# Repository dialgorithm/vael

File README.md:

<h1 align="center">
  vael
  <br>
</h1>

<h4 align="center">
esp32-s3 n8r8 flight controller for sensing and data logging.
</h4>

## it features

- **ESP32-S3-WROOM-1-N8R8** as the main controller
- **MPU6050** 3-axis accelerometer and gyroscope for motion and orientation data
- **BMP180** digital pressure sensor for pressure and altitude-related measurements
- **MicroSD card storage** for flight data logging
- **USB-C connectivity** for programming, debugging, and data transfer
- **TP4056-based LiPo charging** circuitry
- **DW01A battery protection** for LiPo protection
- **MT3608 boost converter** for generating the required higher-voltage rail
- **AMS1117-3.3 LDO** for regulated 3.3 V power
- **USBLC6-2SC6 ESD protection** for USB protection

## design

**vael** is designed to keep the electronics compact while providing enough space for sensors, power circuitry, storage, and connectivity.

the board is built around the **esp32-s3-wroom-1-n8r8**, with the supporting electronics integrated onto a custom pcb. it combines the **imu, pressure sensor, microsd storage, usb-c interface, battery charging, protection, and voltage regulation** into a single compact board.

the layout keeps the sensing and processing electronics centralized while separating the power and signal sections. the **mpu6050** and **bmp180** are positioned for consistent sensor measurements, while the **microsd slot, usb-c connector, battery connector, reset button, and mode switch** are accessible from the board edges.

the board primarily uses **smd components**, including 1206 passives and compact sensor packages, to maintain a small form factor while providing the hardware required for **data collection, logging, and embedded flight applications**.

## Schematics + PCB

| Schematic                           | PCB                    | 3d                       |
| ----------------------------------- | ---------------------- | ------------------------ |
|  |  |  |

## BOM

the complete bill of materials is available in [`bom.csv`](bom.csv).

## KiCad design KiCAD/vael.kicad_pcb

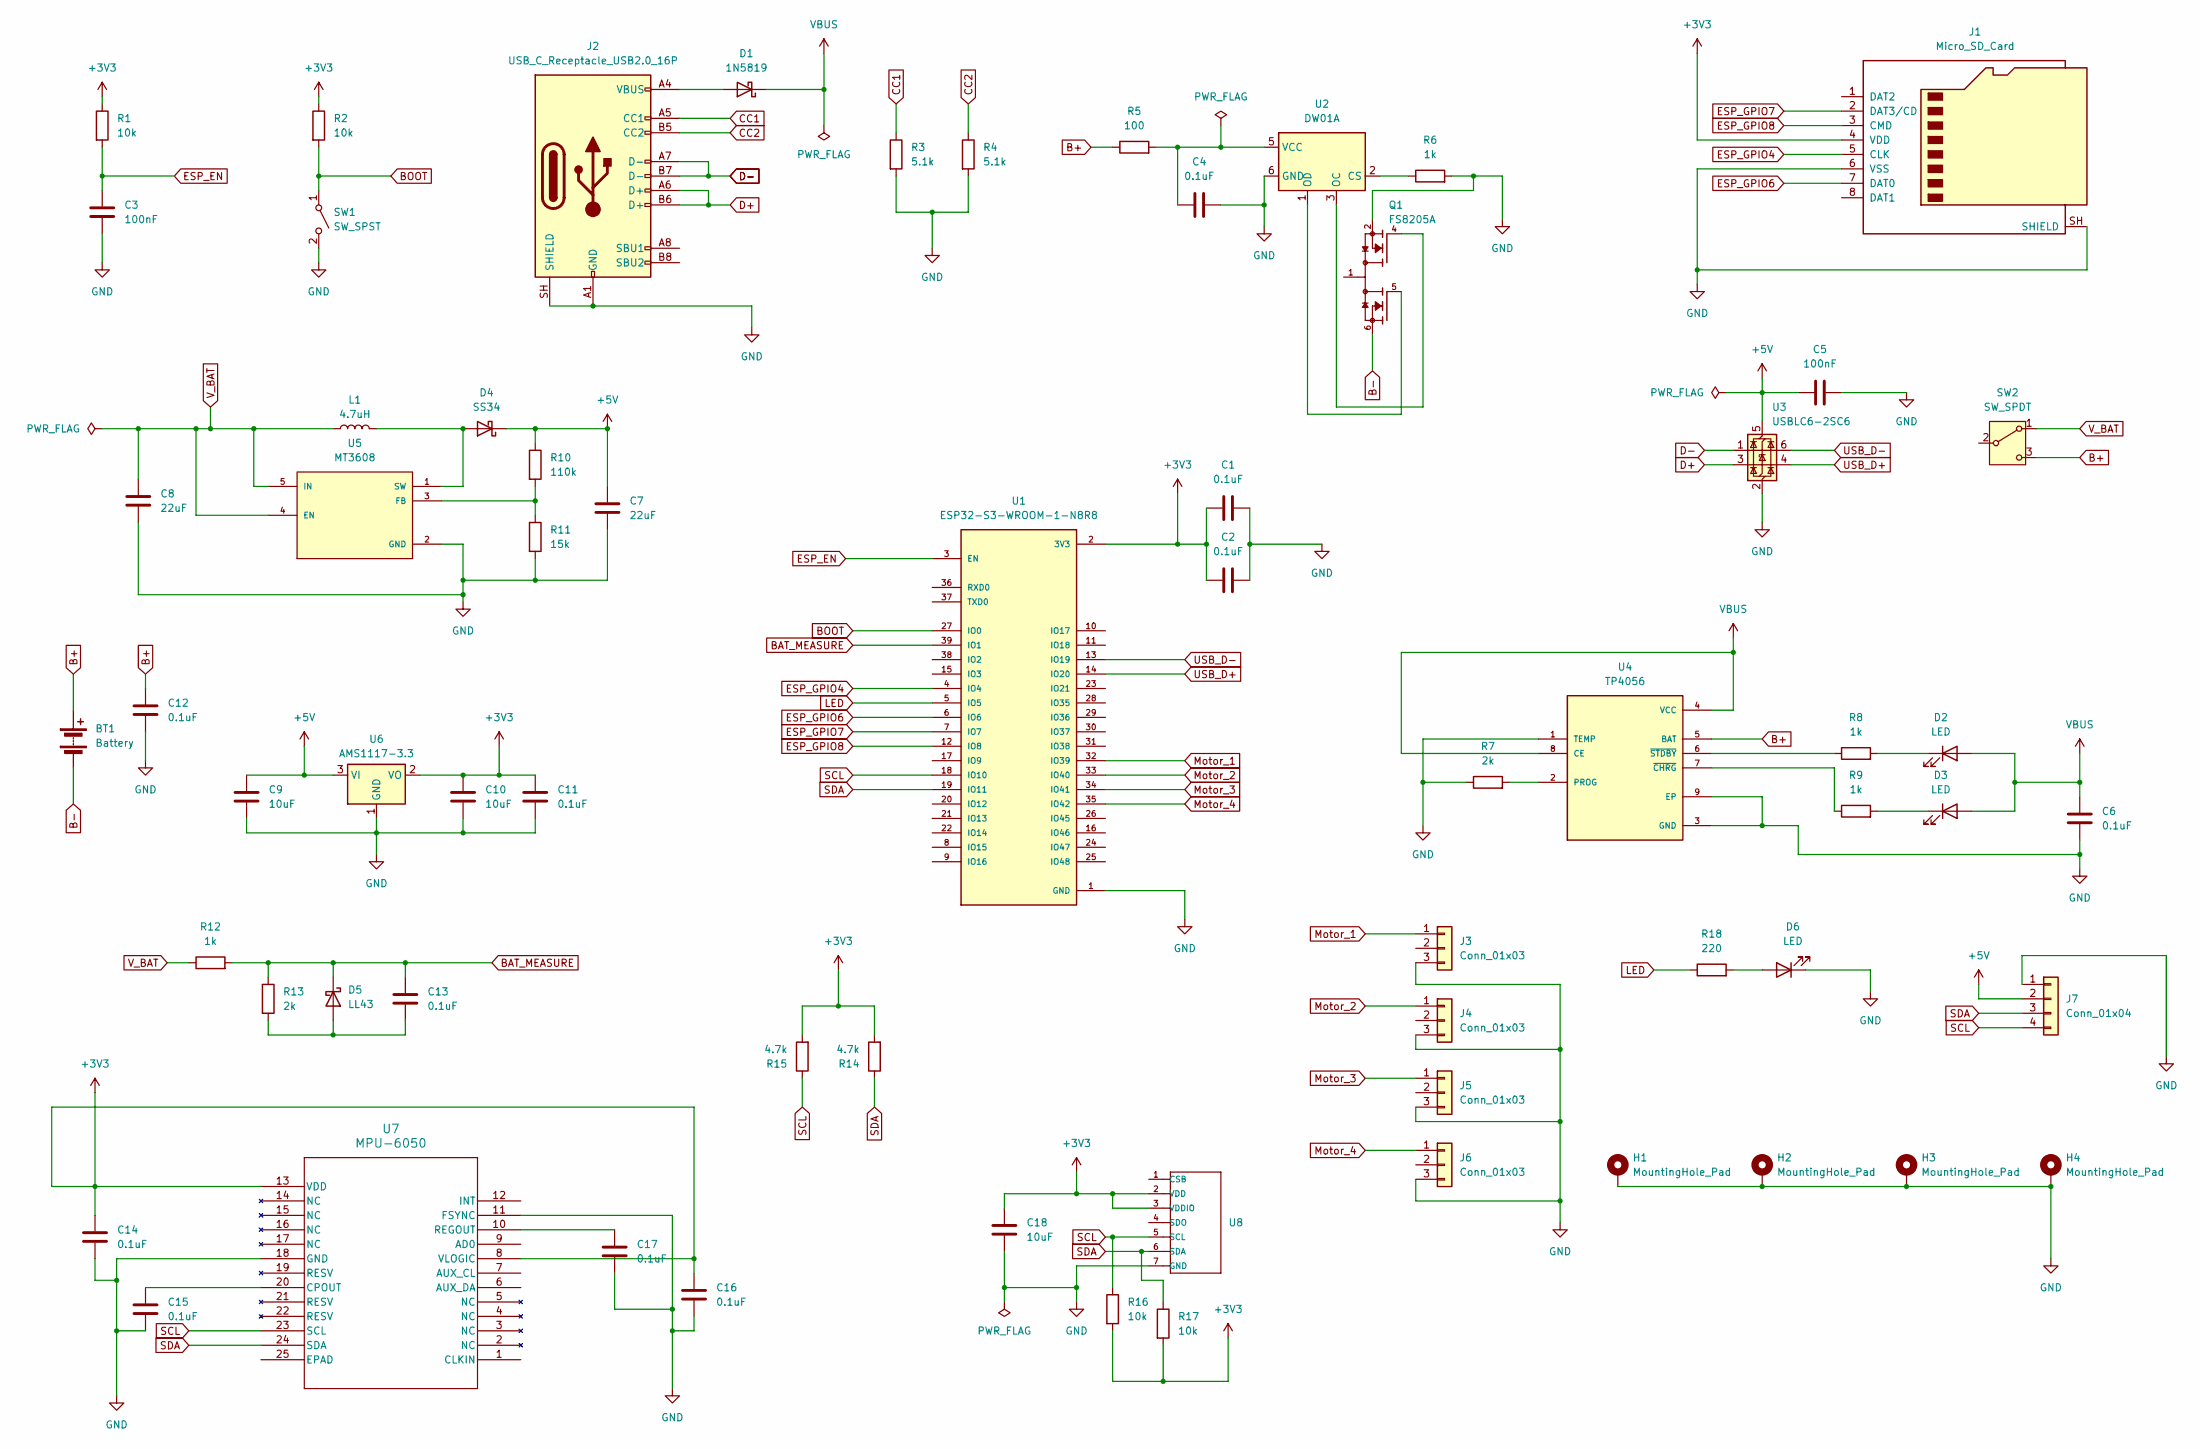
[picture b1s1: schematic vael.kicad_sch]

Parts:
BT1: Battery; JST_XH_B2B-XH-A_1x02_P2.50mm_Vertical
C1, C2, C4, C6, C11, C12, C13, C14, C15, C16, C17: 0.1uF; C_1206_3216Metric_Pad1.33x1.80mm_HandSolder
C3, C5: 100nF; C_1206_3216Metric_Pad1.33x1.80mm_HandSolder
C7, C8: 22uF; C_1206_3216Metric_Pad1.33x1.80mm_HandSolder
C9, C10, C18: 10uF; C_1206_3216Metric_Pad1.33x1.80mm_HandSolder
D1: 1N5819; D_DO-41_SOD81_P10.16mm_Horizontal
D2, D3, D6: LED; LED_1206_3216Metric_Pad1.42x1.75mm_HandSolder
D4: SS34; D_SMA
D5: LL43; D_MiniMELF
H1, H2, H3, H4: MountingHole_Pad; MountingHole_3.2mm_M3_DIN965_Pad
J1: Micro_SD_Card; microSD_HC_Hirose_DM3AT-SF-PEJM5
J2: USB_C_Receptacle_USB2.0_16P; USB_C_Receptacle_GCT_USB4105-xx-A_16P_TopMnt_Horizontal
J3, J4, J5, J6: Conn_01x03; PinHeader_1x03_P2.54mm_Vertical
J7: Conn_01x04; PinHeader_1x04_P2.54mm_Vertical
L1: 4.7uH; L_1206_3216Metric_Pad1.22x1.90mm_HandSolder
Q1: FS8205A; SOP65P640X120-8N; PARTREV 1.7
R1, R2, R16, R17: 10k; R_1206_3216Metric_Pad1.30x1.75mm_HandSolder
R3, R4: 5.1k; R_1206_3216Metric_Pad1.30x1.75mm_HandSolder
R5: 100; R_1206_3216Metric_Pad1.30x1.75mm_HandSolder
R6, R8, R9, R12: 1k; R_1206_3216Metric_Pad1.30x1.75mm_HandSolder
R7, R13: 2k; R_1206_3216Metric_Pad1.30x1.75mm_HandSolder
R10: 110k; R_1206_3216Metric_Pad1.30x1.75mm_HandSolder
R11: 15k; R_1206_3216Metric_Pad1.30x1.75mm_HandSolder
R14, R15: 4.7k; R_1206_3216Metric_Pad1.30x1.75mm_HandSolder
R18: 220; R_1206_3216Metric_Pad1.30x1.75mm_HandSolder
SW1: SW_SPST; SW_PUSH_6mm
SW2: SW_SPDT; SW_SPDT_PCM12
U1: ESP32-S3-WROOM-1-N8R8; XCVR_ESP32S3WROOM1N8R8
U2: DW01A; SOT-23-6
U3: USBLC6-2SC6; SOT-23-6
U4: TP4056; SOP127P600X175-9N
U5: MT3608; SOT95P280X145-6N; PARTREV 1.0
U6: AMS1117-3.3; SOT-223-3_TabPin2
U7: MPU-6050; QFN24_4X4X0P9-0P5_TDK
U8: BMP18; LGA7-1.5-3.8X3.6MM; MPN BMP18

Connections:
+3V3: C1.1, C2.1, C10.1, C11.1, C14.1, C16.1, C18.1, J1.4 (VDD), R1.1, R2.1, R14.2, R15.2, R16.2, R17.2, U1.2 (3V3), U6.2 (VO), U7.8 (VLOGIC), U7.13 (VDD), U8.2 (VDD), U8.3 (VDDIO)
+5V: C5.1, C7.1, C9.1, D4.1 (K), J7.2, R10.1, U3.5 (VBUS), U6.3 (VI)
B+: BT1.1 (+), C12.1, R5.1, SW2.3 (C), U4.5 (BAT)
B-: BT1.2 (-), Q1.6, Q1.7
BAT_MEASURE: C13.1, D5.1 (K), R12.2, R13.1, U1.39 (IO1)
BOOT: R2.2, SW1.1 (A), U1.27 (IO0)
CC1: J2.A5 (CC1), R3.1
CC2: J2.B5 (CC2), R4.1
D+: J2.A6 (D+), J2.B6 (D+), U3.3 (I/O2)
D-: J2.A7 (D-), J2.B7 (D-), U3.1 (I/O1)
ESP_EN: C3.1, R1.2, U1.3 (EN)
ESP_GPIO4: J1.5 (CLK), U1.4 (IO4)
ESP_GPIO6: J1.7 (DAT0), U1.6 (IO6)
ESP_GPIO7: J1.2 (DAT3/CD), U1.7 (IO7)
ESP_GPIO8: J1.3 (CMD), U1.12 (IO8)
GND: C1.2, C2.2, C3.2, C4.2, C5.2, C6.2, C7.2, C8.2, C9.2, C10.2, C11.2, C12.2, C14.2, C15.2, C16.2, C17.2, C18.2, D6.1 (K), H1.1 (1_1), H2.1 (1_1), H3.1 (1_1), H4.1 (1_1), J1.6 (VSS), J1.SH (SHIELD), J2.A1 (GND), J2.A12 (GND), J2.B1 (GND), J2.B12 (GND), J2.SH (SHIELD), J3.3, J4.3, J5.3, J6.3, J7.1, Q1.2, Q1.3, R3.2, R4.2, R6.2, R7.1, R11.2, SW1.2 (B), U1.1 (GND), U1.40 (GND), U1.41_1 (GND), U1.41_2 (GND), U1.41_3 (GND), U1.41_4 (GND), U1.41_5 (GND), U1.41_6 (GND), U1.41_7 (GND), U1.41_8 (GND), U1.41_9 (GND), U2.6 (GND), U3.2 (GND), U4.1 (TEMP), U4.3 (GND), U4.9 (EP), U5.2 (GND), U6.1 (GND), U7.11 (FSYNC), U7.18 (GND), U8.7 (GND)
LED: R18.1, U1.5 (IO5)
Motor_1: J3.1, U1.32 (IO39)
Motor_2: J4.1, U1.33 (IO40)
Motor_3: J5.1, U1.34 (IO41)
Motor_4: J6.1, U1.35 (IO42)
unnamed: D1.2 (A), J2.A4 (VBUS), J2.A9 (VBUS), J2.B4 (VBUS), J2.B9 (VBUS)
unnamed: D2.1 (K), R8.2
unnamed: D3.1 (K), R9.2
unnamed: D4.2 (A), L1.2, U5.1 (SW)
unnamed: C13.2, D5.2 (A), R13.2
unnamed: D6.2 (A), R18.2
unnamed: Q1.1, Q1.8
unnamed: R6.1, U2.2 (CS)
unnamed: Q1.4, U2.3 (OC)
unnamed: Q1.5, U2.1 (OD)
unnamed: C4.1, R5.2, U2.5 (VCC)
unnamed: R7.2, U4.2 (PROG)
unnamed: R9.1, U4.7 (~CHRG)
unnamed: R8.1, U4.6 (~STDBY)
unnamed: R10.2, R11.1, U5.3 (FB)
unnamed: C15.1, U7.20 (CPOUT)
unnamed: C17.1, U7.10 (REGOUT)
SCL: J7.4, R15.1, R16.1, U1.18 (IO10), U7.23 (SCL), U8.5 (SCL)
SDA: J7.3, R14.1, R17.1, U1.19 (IO11), U7.24 (SDA), U8.6 (SDA)
USB_D+: U1.14 (IO20), U3.4 (I/O2)
USB_D-: U1.13 (IO19), U3.6 (I/O1)
VBUS: C6.1, D1.1 (K), D2.2 (A), D3.2 (A), U4.4 (VCC), U4.8 (CE)
V_BAT: C8.1, L1.1, R12.1, SW2.1 (A), U5.4 (EN), U5.5 (IN)

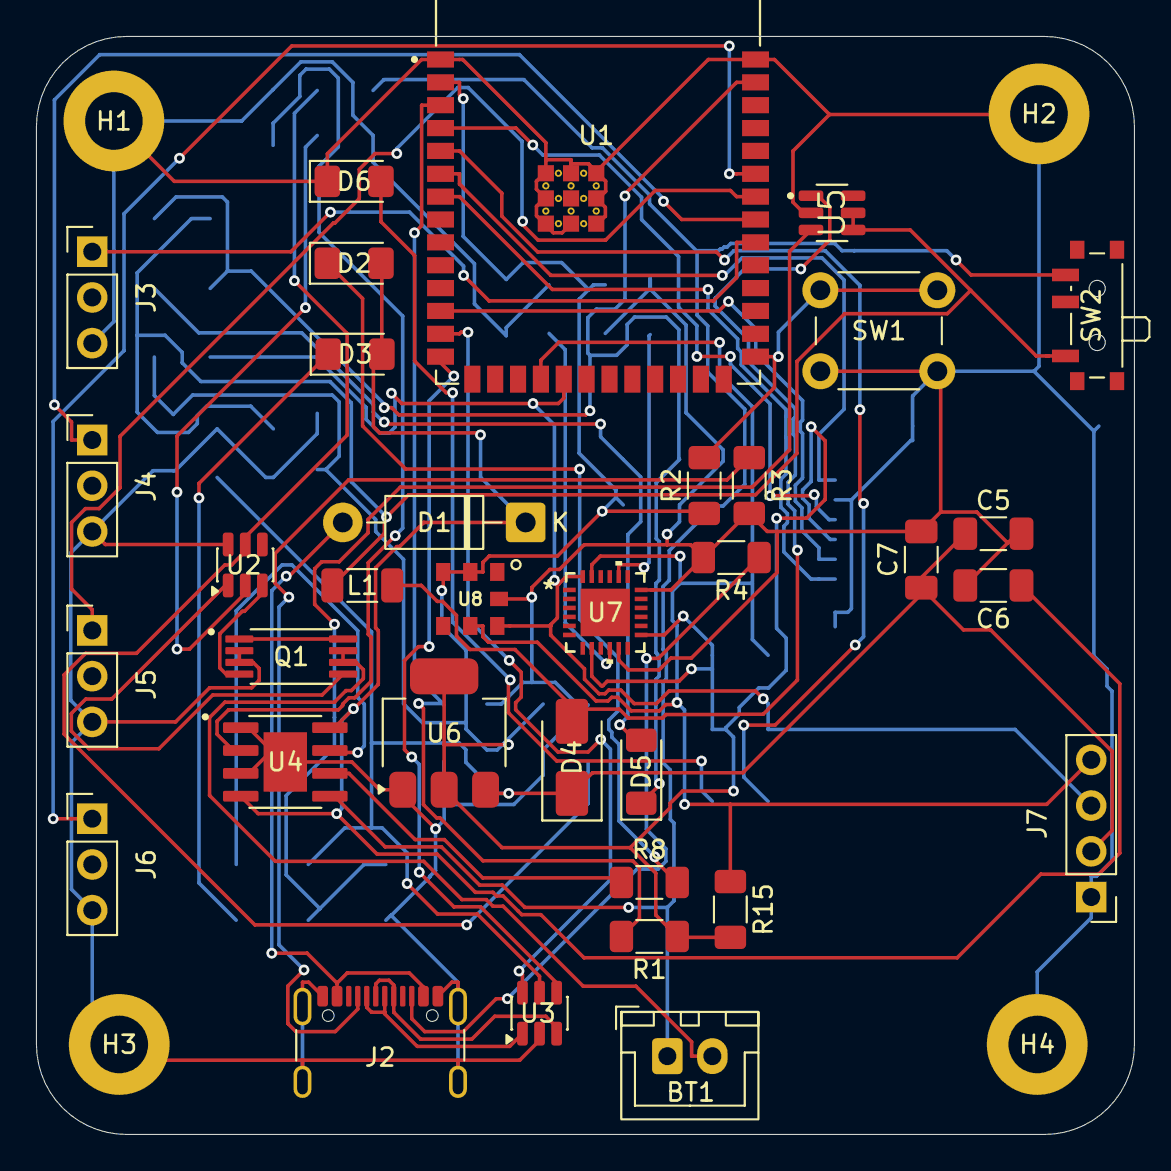
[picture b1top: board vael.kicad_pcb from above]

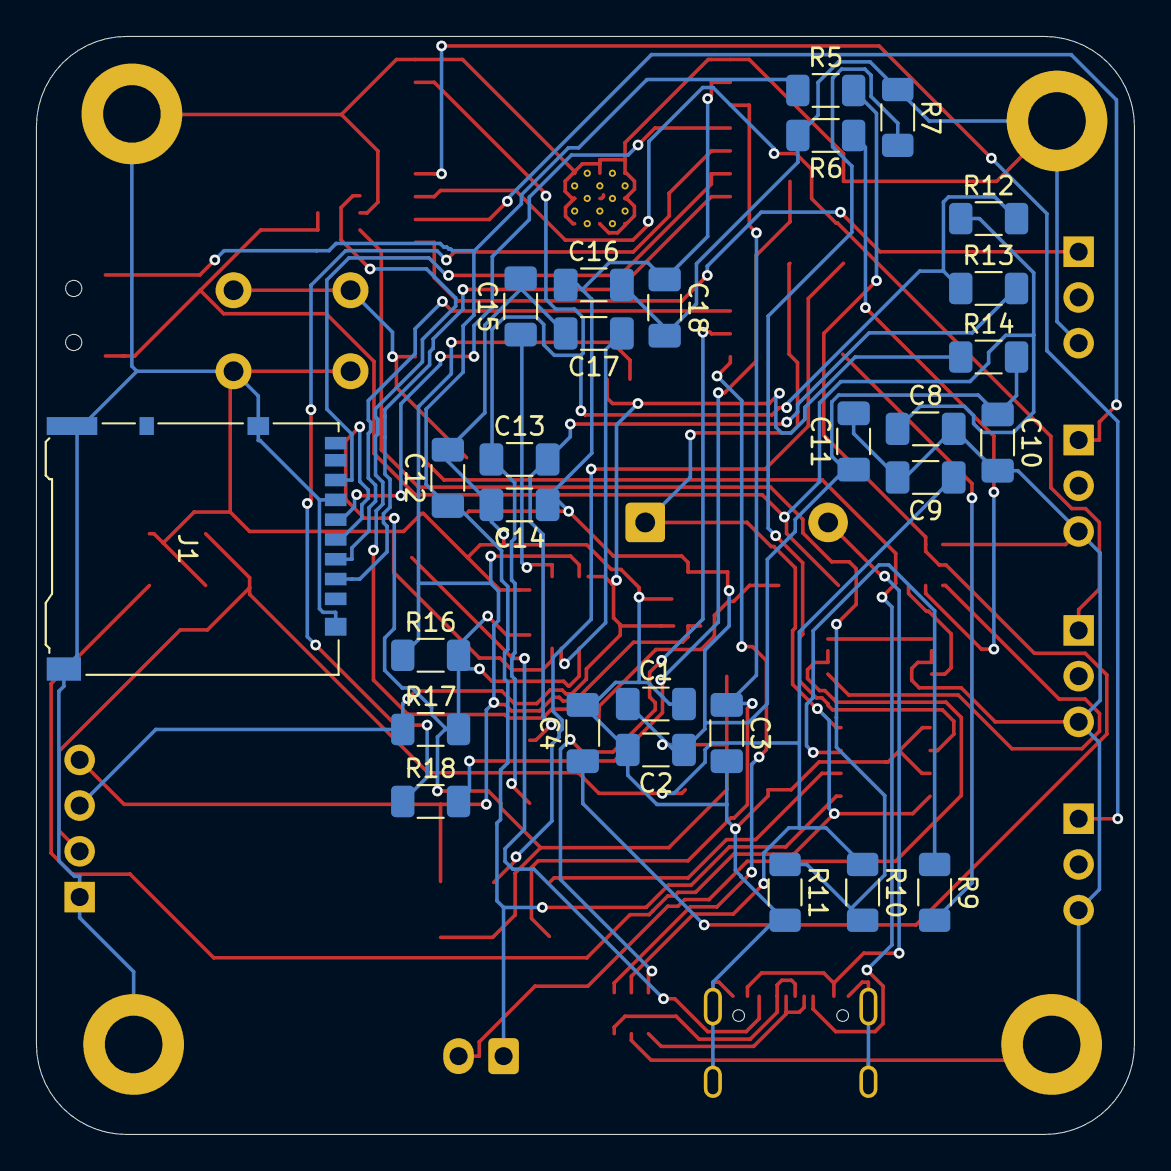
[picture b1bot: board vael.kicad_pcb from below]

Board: 2 copper layers, 61.0 x 61.0 mm, 66 parts (28 on the bottom side), 44 nets.

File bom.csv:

component, qty, cost, why, source
pcb, 5, $13, main, https://robu.in/product/online-pcb-manufacturing-service/
JST XH Pitch Plug and Socket, 2, $0.5, connect battery, https://robu.in/product/2-pin-jst-xh-2-54mm-pitch-plug-and-s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
0.1uF 1206 Capacitor, 22, $1, 11 per pcb, https://robu.in/product/0-1uf-capacitor-smdc-1206/
10uF 1206 Capacitor, 6, $1.3, 3 per pcb, https://robu.in/product/10uf-10000nf-50v-capacitor-1206-smd-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
100nF 1206 Capacitor, 5, $0.5, 2 per pcb, https://robu.in/product/100nf-1206-surface-mount-multilayer-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
22uF 1206 Capacitor, 5, $0.5, 2 per pcb, https://robu.in/product/1206x226m250nt-fh-25v-22uf-x5r%c2%b1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
1N5819 Schottky Diodes, 2, $0.9, one way current flow, https://robu.in/product/1-month-warranty-1053/
LED 1206 Package, 6, $0.8, 3 per pcb, https://robu.in/product/xl-3216uoc-fb-xinglight-reverse-moun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
SS34 Schottky Diodes ROHS, 2, $2.3, non reversible current, https://robu.in/product/ss34-onsemi-40v-500mv3a-3a-smcdo-214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
LL43-GS08 Rectifier Diode, 2, $3, no current backflow, https://www.lioncircuits.com/parts/LL43-GS08
DM3AT-SF-PEJM5 Micro SD socket, 2, $13, flight logs, https://www.lioncircuits.com/parts/DM3AT-SF-PEJM5
GCT USB4105 (USB C) Connector, 2, $4, flash and debug, https://www.lioncircuits.com/parts/USB4105-GF-A
2.54mm Male pin header, 10, $3, for motor connections, https://robu.in/product/2-54mm-1x40-pin-male-single-row-stra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
4.7uH 120p6 Inductor, 2, $2.2, for impedance, https://robu.in/product/lqm31pn4r7m00l-murata-electronics-70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
FS8205A Mosfets, 5, $1, , https://robu.in/product/1-month-warranty-398/
10k 1206 Resistors, 8, $1, 4 per pcb, https://robu.in/product/rc1206fr-0710kl-yageo-res-thick-film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
110k 1206 Resistors, 5, $1, resist current, https://robu.in/product/1206w4f1103t5e-uniohm-royal-ohm-250m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
15k 1206 Resistors, 5, $1, resist current, https://robu.in/product/1206w4f1502t5e-uniohm-royal-ohm-250m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
1k 1206 Resistors, 8, $1, 4 per pcb, https://robu.in/product/wr12x1001ftl-walsin-250mw-thick-film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
2k 1206 Resistors, 4, $1, 2 per pcb, https://robu.in/product/wr12x2001ftl-walsin-250mw-thick-film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
4.7k 1206 Resistors, 4, $1, 2 per pcb, https://robu.in/product/rc1206fr-104k7l-yageo-250mw-thick-fi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
220 1206 Resistors, 5, $1, resist current, https://robu.in/product/1206w4f2200t5e-uniohm-royal-ohm-250m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
5.1k 1206 Resistors, 4, $1, 2 per pcb, https://robu.in/product/1206w4f5101t5e-uniohm-royal-ohm-250m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
100 1206 Resistors, 5, $1, resist current, https://robu.in/product/ac1206fr-07100rl-yageo-res-thick-fil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
6x6x5mm Tactile Push Button Switch, 2, $1, reset clicky, https://robu.in/product/6x6x5mm-tactile-push-button-switch-p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
Mini Slide Switch 7Pin SMD, 2, $1, mode slide switch, https://sharvielectronics.com/product/mini-slide-switch-7pin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
ESP32-S3-WROOM-1-N8R8, 2, $13.8, brain, https://robu.in/product/espressif-esp32-s3-wroom-1-n8r8-modules/
DW01A Battery Protection IC, 2, $1, protect pcb, https://robu.in/product/dw01a-4-3v-lithium-ion-lithium-polym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
USBLC6-2SC6 ESD and Surge Protection IC, 2, $1, protect pcb, https://robu.in/product/usblc6-2sc6-ms-msksemi-4-5a-15v-150w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
TP4056 SOP-8 SMD Package, 2, $1, battery charging, https://robu.in/product/1-month-warranty-1253/
MT3608 DC Boost converter, 2, $1, 3.3v ==> 5v, https://robu.in/product/mt3608-xian-aerosemi-tech-boost-type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
AMS1117-3.3 LDO Regulators, 2, $1, regulates voltage, https://robu.in/product/1-month-warranty-385/
MPU 6050 QFN-24 3-Axis Gyro/Accelerometer IC, 2, $11.6, orientation and position data, https://zbotic.in/product/mpu-6050-qfn-24-3-axis-gyro-accele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
BMP180 LGA-7 Digital Pressure Sensor IC, 2, $5.2, pressure data, https://sharvielectronics.com/product/bmp180-digital-pressur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
8GB MicroSD Card, 2, $8.4, data logging, https://sharvielectronics.com/product/8gb-memory-card-sandisk/
Total, -, $110, -, -

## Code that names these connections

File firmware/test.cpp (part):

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#define SD_CS_PIN           10

// Motor / actuator outputs
#define MOTOR_1_PIN         4
#define MOTOR_2_PIN         5
#define MOTOR_3_PIN         6
#define MOTOR_4_PIN         7


// ============================================================
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        motor4 = throttle;
    }

    writeMotor(MOTOR_1_PIN, motor1);
    writeMotor(MOTOR_2_PIN, motor2);
    writeMotor(MOTOR_3_PIN, motor3);
    writeMotor(MOTOR_4_PIN, motor4);
}


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    // --------------------------------------------------------

    ledcAttach(
        MOTOR_1_PIN,
        PWM_FREQUENCY,
        PWM_RESOLUTION
    );

    ledcAttach(
        MOTOR_2_PIN,
        PWM_FREQUENCY,
        PWM_RESOLUTION
    );

    ledcAttach(
        MOTOR_3_PIN,
        PWM_FREQUENCY,
        PWM_RESOLUTION
    );

    ledcAttach(
        MOTOR_4_PIN,
        PWM_FREQUENCY,
        PWM_RESOLUTION
    );

    // Always start outputs at minimum.
    writeMotor(MOTOR_1_PIN, MOTOR_IDLE);
    writeMotor(MOTOR_2_PIN, MOTOR_IDLE);
    writeMotor(MOTOR_3_PIN, MOTOR_IDLE);
    writeMotor(MOTOR_4_PIN, MOTOR_IDLE);

    // --------------------------------------------------------
    // SD
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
